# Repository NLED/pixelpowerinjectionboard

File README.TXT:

THERE IS NO WARRANTY FOR THE PROGRAM, TO THE EXTENT PERMITTED BY APPLICABLE LAW. 
EXCEPT WHEN OTHERWISE STATED IN WRITING THE COPYRIGHT HOLDERS AND/OR OTHER PARTIES 
PROVIDE THE PROGRAM “AS IS” WITHOUT WARRANTY OF ANY KIND, EITHER EXPRESSED OR IMPLIED,
INCLUDING, BUT NOT LIMITED TO, THE IMPLIED WARRANTIES OF MERCHANTABILITY AND FITNESS 
FOR A PARTICULAR PURPOSE. THE ENTIRE RISK AS TO THE QUALITY AND PERFORMANCE OF THE 
PROGRAM IS WITH YOU. SHOULD THE PROGRAM PROVE DEFECTIVE, YOU ASSUME THE COST OF ALL 
NECESSARY SERVICING, REPAIR OR CORRECTION.

 Original Author: Jeffrey Nygaard
 Company: Northern Lights Electronic Design, LLC
 Date: March 5, 2018
 Contact: JNygaard@NLEDshop.com
 Copyright© 2018 by Northern Lights Electronic Design, LLC. All Rights Reserved
 
;=============          www.NLEDShop.com/pixelproducts          ============
;=============     www.NorthernLightsElectronicDesign.com       ============

This work is licensed under a Attribution-NonCommercial 4.0 International (CC BY-NC 4.0)
https://creativecommons.org/licenses/by-nc/4.0/legalcode

Free to use for personal use, but please attribute the original author.

Commercial licenses versions are available for a donation of any amount. Contact JNygaard@NLEDshop.com for details.

================================================================================================================

Ready-made devices are available for purchase, and large batch manufacturing of any device can be requested.
Please see the webpage www.NLEDShop.com/pixelproducts

NLED is available for custom design and manufacturing, please contact via phone or email to discuss your project.

================================================================================================================

Pixel Power Injection Board:
	A passive device that allows a pixel string to be 'injected' with power from a 2.1x5.5mm barrel jack or with screw terminals. This does not do anything to the data signal other than pass it thru.
	
	BOM:
		PCB: 1.5" x 1.5", 1.6mm thick
		DC Jack Part#: Wurth 694106301002
		Capacitor: 3.5mm x 8mm, 220uF. Example: UHV1V221MPD
		Terminals: 5.08mm spaced, 5x 2-pinsGeneric, Example Part# OSTTC022162
		
Included Files:
	Eagle Schematic and Board Files
	Wiring Diagrams and Datasheet

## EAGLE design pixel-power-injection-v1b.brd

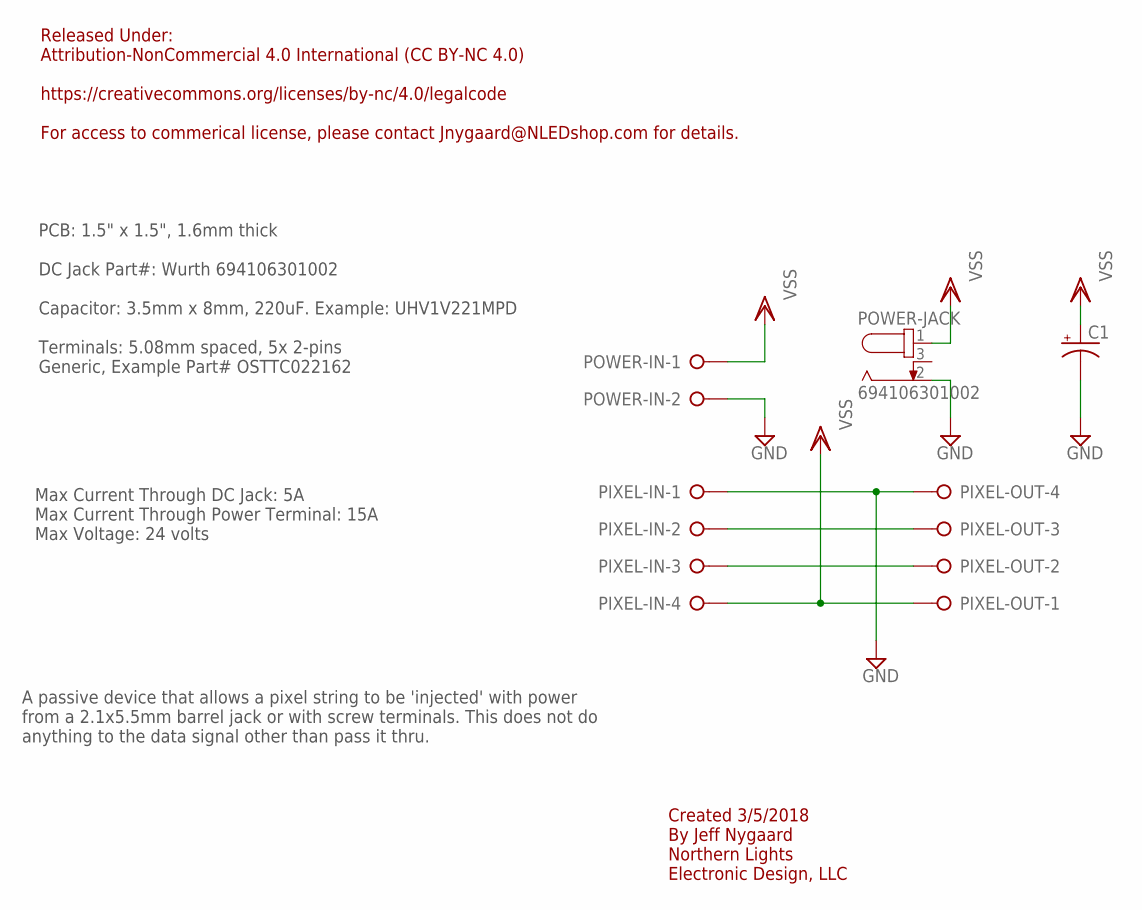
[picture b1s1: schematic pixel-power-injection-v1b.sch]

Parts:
C1: CPOL-USE3.5-8; E3,5-8
PIXEL-IN: W237-04P; W237-4P
PIXEL-OUT: W237-04P; W237-4P
POWER-IN: W237-02P; W237-132
POWER-JACK: 694106301002

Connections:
GND: C1.-, PIXEL-IN.1, PIXEL-OUT.4, POWER-IN.2, POWER-JACK.2
unnamed: PIXEL-IN.3, PIXEL-OUT.2
unnamed: PIXEL-IN.2, PIXEL-OUT.3
VSS: C1.+, PIXEL-IN.4, PIXEL-OUT.1, POWER-IN.1, POWER-JACK.1

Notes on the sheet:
Released Under: Attribution-NonCommercial 4.0 International (CC BY-NC 4.0) https://creativecommons.org/licenses/by-nc/4.0/legalcode For access to commerical license, please contact Jnygaard@NLEDshop.com for details.
Created 3/5/2018 By Jeff Nygaard Northern Lights Electronic Design, LLC
PCB: 1.5" x 1.5", 1.6mm thick DC Jack Part#: Wurth 694106301002 Capacitor: 3.5mm x 8mm, 220uF. Example: UHV1V221MPD Terminals: 5.08mm spaced, 5x 2-pins Generic, Example Part# OSTTC022162
Max Current Through DC Jack: 5A Max Current Through Power Terminal: 15A Max Voltage: 24 volts
A passive device that allows a pixel string to be 'injected' with power from a 2.1x5.5mm barrel jack or with screw terminals. This does not do anything to the data signal other than pass it thru.

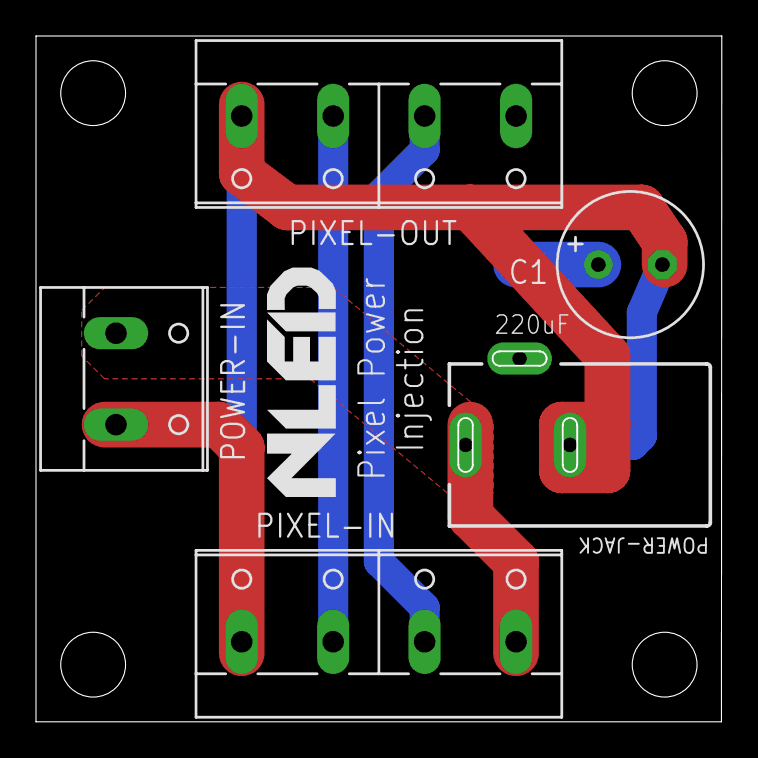
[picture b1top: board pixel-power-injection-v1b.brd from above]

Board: 2 copper layers, 38.0 x 38.0 mm, 5 parts (0 on the bottom side), 4 nets.

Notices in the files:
pixel-power-injection-v1b.brd:
Copyright 2018
parts and their libraries:
Wurth_Elektronik_Electromechanic_DC_Powe: Copyright: Würth Elektronik
